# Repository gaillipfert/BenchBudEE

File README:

The BenchBudEE is the project for the Session 1 course on ContextualElectronics.com. It is a flexible bench multitool, intended to teach a wide range of analog and digital technique and easily interface to the Arduino platform. The hardware files are licensed as Open Source Hardware, so anyone will be able to take the files and modify them (with attribution) or manufacture a finished board. All design files are available on GitHub. The board has the following subcircuits:

    A high level analog input measurement circuit (for +/- 10V and thermocouple measurement)
    A programmable current output.
    A PWM fan control output.
    Power conditioning and fixed voltage output circuits.
    A relay control circuit.
    An LED string driver.

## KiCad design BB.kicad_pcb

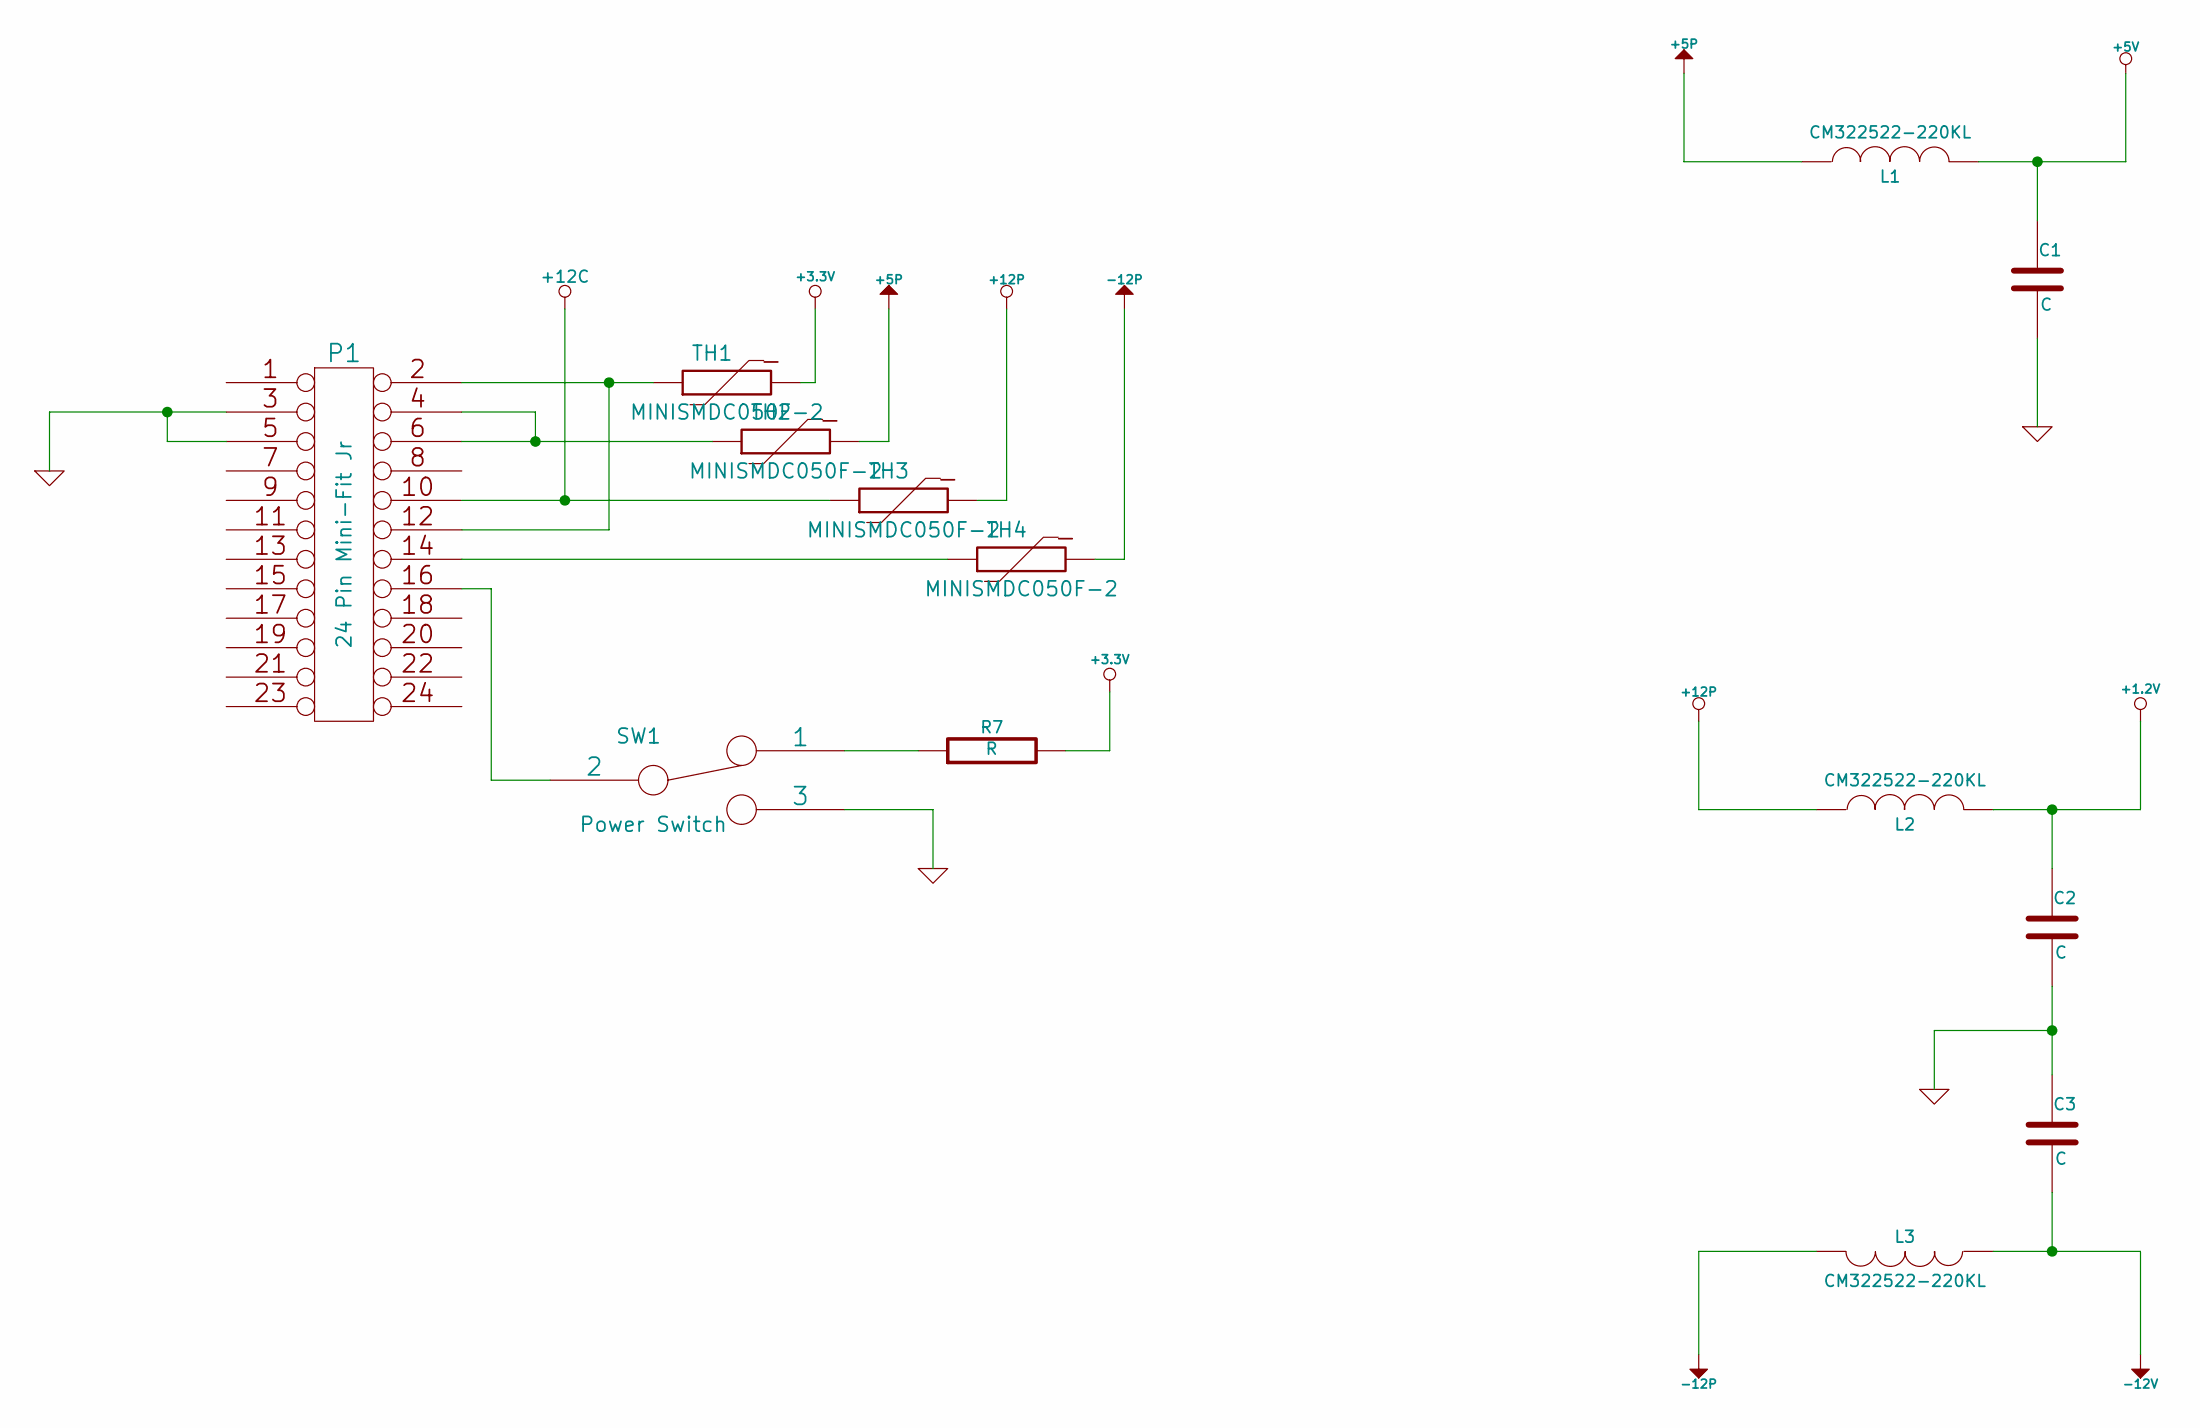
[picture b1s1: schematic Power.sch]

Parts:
C1, C2, C3: C
L1, L2, L3: CM322522-220KL; MFG Part Number CM322522-220KL
P1: 24 Pin Mini-Fit Jr; MFG Part Number 39-30-1240
R7: R
SW1: Power Switch; MFG Part Number OS102011MA1QN1
TH1, TH2, TH3, TH4: MINISMDC050F-2; MFG Part Number MINISMDC050F-2

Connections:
+1.2V: C2.1, L2.2; also elsewhere on the board
+3.3V: R7.2, TH1.2; also elsewhere on the board
+5P: L1.1, TH2.2; also elsewhere on the board
+5V: C1.1, L1.2; also elsewhere on the board
+12C: P1.10, TH3.1; also elsewhere on the board
+12P: L2.1, TH3.2; also elsewhere on the board
-12P: L3.2, TH4.2
-12V: C3.2, L3.1; also elsewhere on the board
GND: C1.2, C2.2, C3.1, P1.3, P1.5, SW1.3; also elsewhere on the board
unnamed: P1.4, P1.6, TH2.1
unnamed: P1.2, P1.12, TH1.1
unnamed: P1.14, TH4.1
unnamed: P1.16, SW1.2
unnamed: R7.1, SW1.1

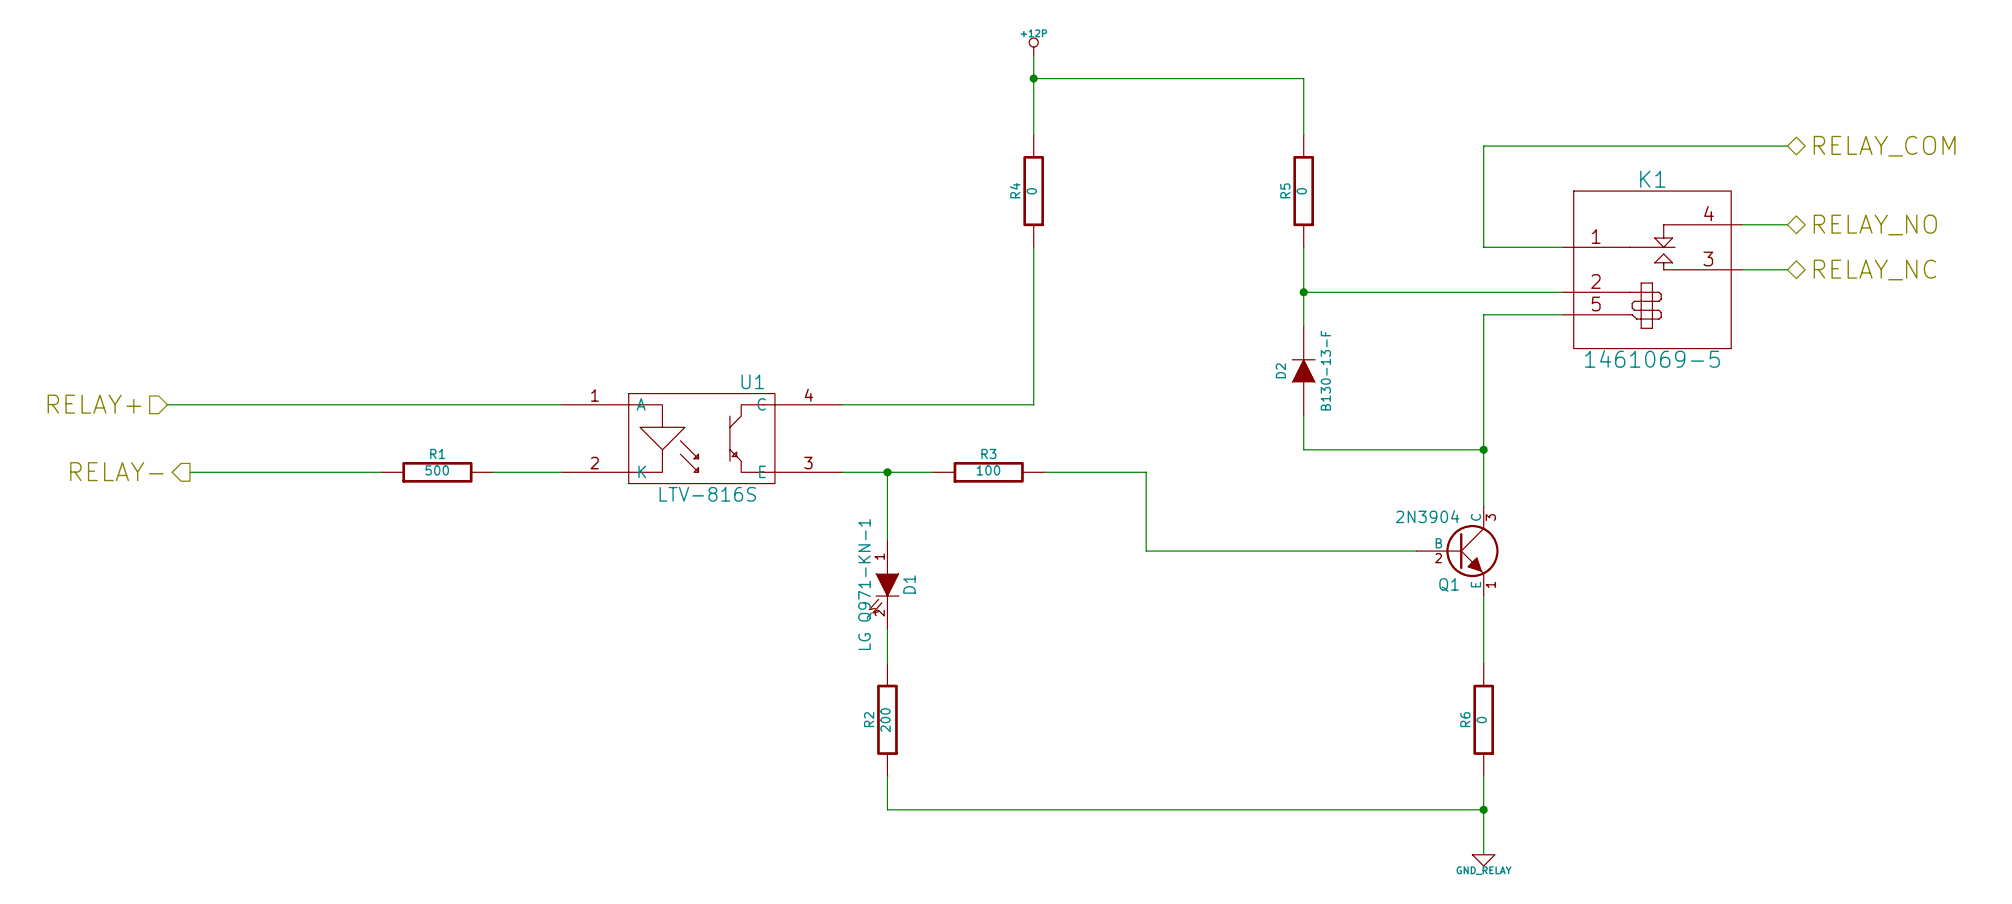
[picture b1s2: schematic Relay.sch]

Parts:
D1: LG Q971-KN-1; MFG Part Number LG Q971-KN-1
D2: B130-13-F; MFG Part Number B130-13-F
K1: 1461069-5; MFG Part Number 1461069-5
Q1: 2N3904; MFG Part Number MMBT3904-7-F
R1: 500
R2: 200
R3: 100
R4, R5, R6: 0
U1: LTV-816S; MFG Part Number LTV-816S

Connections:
+12P: R4.2, R5.2; also elsewhere on the board
/Arduino/RELAY+: U1.1 (A); also elsewhere on the board
/Arduino/RELAY-: R1.1; also elsewhere on the board
/Relay/RELAY_COM: K1.1 (com); also elsewhere on the board
/Relay/RELAY_NC: K1.3 (no); also elsewhere on the board
/Relay/RELAY_NO: K1.4 (NC); also elsewhere on the board
GND_RELAY: R2.1, R6.1
unnamed: D1.1 (A), R3.1, U1.3 (E)
unnamed: D1.2 (K), R2.2
unnamed: D2.1 (A), K1.5 (coil1), Q1.3 (C)
unnamed: D2.2 (K), K1.2 (coil+), R5.1
unnamed: Q1.1 (E), R6.2
unnamed: Q1.2 (B), R3.2
unnamed: R1.2, U1.2 (K)
unnamed: R4.1, U1.4 (C)

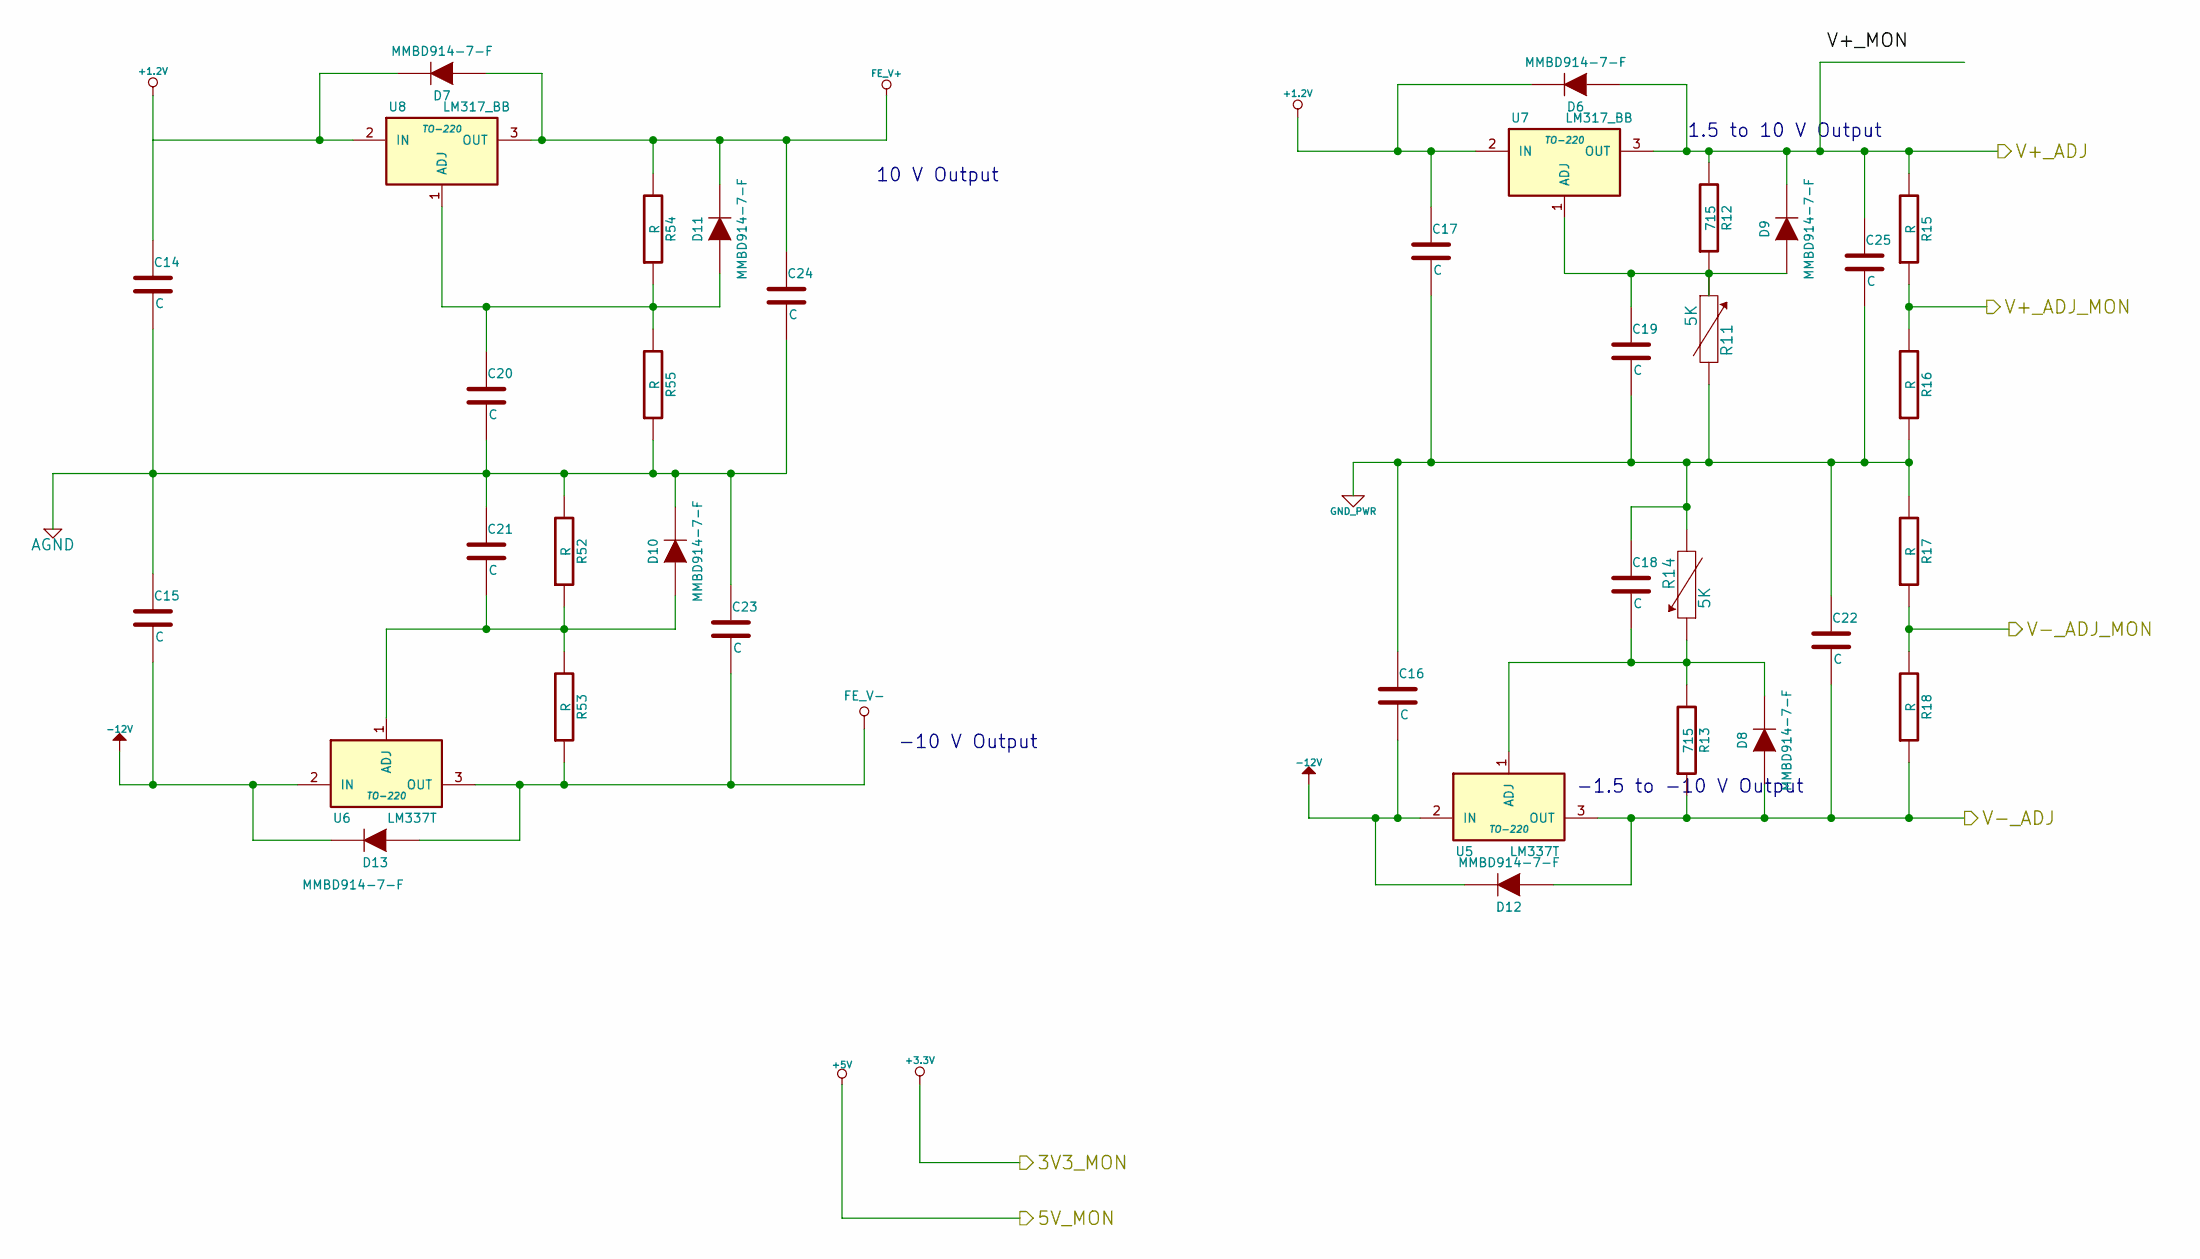
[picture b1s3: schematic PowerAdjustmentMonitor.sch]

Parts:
C14, C15, C16, C17, C18, C19, C20, C21, C22, C23, C24, C25: C
D6, D7, D8, D9, D10, D11, D12, D13: MMBD914-7-F; MFG Part Number MMBD914-7-F
R11, R14: 5K
R12, R13: 715
R15, R16, R17, R18, R52, R53, R54, R55: R
U5, U6: LM337T; TO-220
U7, U8: LM317_BB; TO-220

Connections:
+1.2V: C14.1, C17.1, D6.2 (K), U7.2 (IN); also elsewhere on the board
-12V: C15.2, C16.2, D12.2 (K), D13.2 (K), U5.2 (IN), U6.2 (IN); also elsewhere on the board
/Arduino/V+_ADJ_MON: R15.1, R16.2; also elsewhere on the board
/Arduino/V-_ADJ_MON: R17.1, R18.2; also elsewhere on the board
/PowerAdjustmentMonitor/V+_ADJ: C25.1, D6.1 (A), D9.2 (K), R12.2, R15.2, U7.3 (OUT); also elsewhere on the board
/PowerAdjustmentMonitor/V-_ADJ: C22.2, D8.1 (A), D12.1 (A), R13.1, R18.1, U5.3 (OUT); also elsewhere on the board
AGND: C14.2, C15.1, C20.2, C21.1, C23.1, C24.2, D10.2 (K), R52.2, R55.1; also elsewhere on the board
FE_V+: C24.1, D7.1 (A), D11.2 (K), R54.2, U8.3 (OUT); also elsewhere on the board
FE_V-: C23.2, D13.1 (A), R53.1, U6.3 (OUT); also elsewhere on the board
GND_PWR: C16.1, C17.2, C18.1, C19.2, C22.1, C25.2, R11.2, R14.2, R16.1, R17.2; also elsewhere on the board
unnamed: C18.2, D8.2 (K), R13.2, R14.1, U5.1 (ADJ)
unnamed: C19.1, D9.1 (A), R11.1, R12.1, U7.1 (ADJ)
unnamed: C20.1, D11.1 (A), R54.1, R55.2, U8.1 (ADJ)
unnamed: C21.2, D10.1 (A), R52.1, R53.2, U6.1 (ADJ)
unnamed: D7.2 (K), U8.2 (IN)

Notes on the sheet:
1.5 to 10 V Output
10 V Output
-10 V Output
-1.5 to -10 V Output

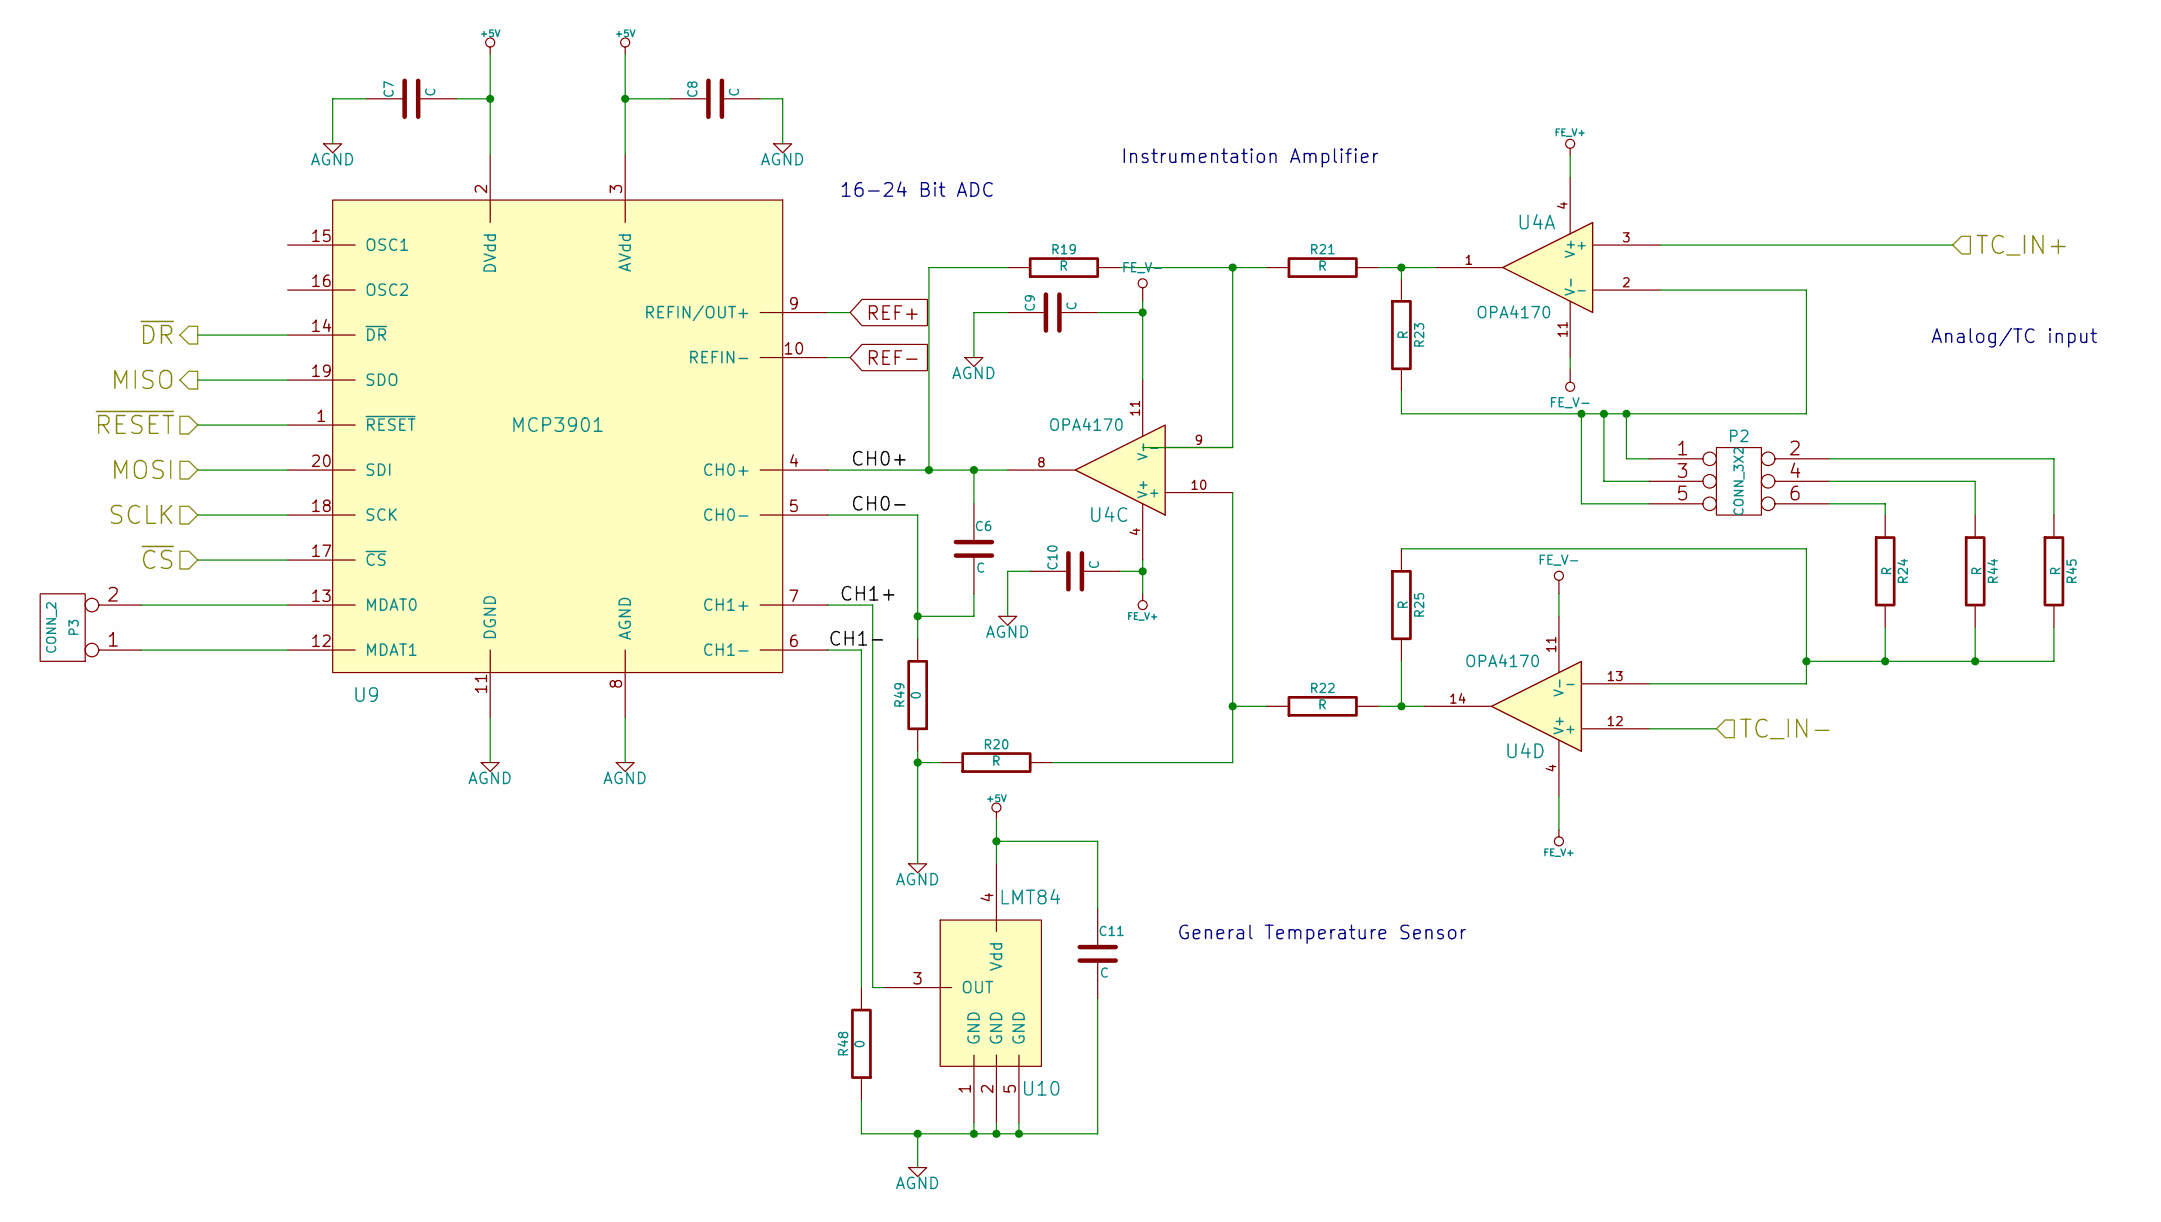
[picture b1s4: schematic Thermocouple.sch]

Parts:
C6, C7, C8, C9, C10, C11: C
P2: CONN_3X2
P3: CONN_2
R19, R20, R21, R22, R23, R24, R25, R44, R45: R
R48, R49: 0
U4: OPA4170
U9: MCP3901
U10: LMT84

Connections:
+5V: C7.2, C8.1, C11.1, U9.2 (DVdd), U9.3 (AVdd), U10.4 (Vdd); also elsewhere on the board
/Arduino/MISO: U9.19 (SDO); also elsewhere on the board
/Arduino/MOSI: U9.20 (SDI); also elsewhere on the board
/Arduino/SCLK: U9.18 (SCK); also elsewhere on the board
/Arduino/~ADC_CS: U9.17 (~CS); also elsewhere on the board
/Arduino/~DR: U9.14 (~DR); also elsewhere on the board
/Arduino/~RESET: U9.1 (~RESET); also elsewhere on the board
/TerminalBlock/TC_IN+: U4.3 (+); also elsewhere on the board
/TerminalBlock/TC_IN-: U4.12 (+); also elsewhere on the board
/Thermocouple/CH0+: C6.1, R19.1, U4.8, U9.4 (CH0+)
/Thermocouple/CH0-: C6.2, R49.2, U9.5 (CH0-)
/Thermocouple/CH1+: U9.7 (CH1+), U10.3 (OUT)
/Thermocouple/CH1-: R48.2, U9.6 (CH1-)
AGND: C7.1, C8.2, C9.1, C10.1, C11.2, R20.1, R48.1, R49.1, U9.8 (AGND), U9.11 (DGND), U10.1 (GND), U10.2 (GND), U10.5 (GND); also elsewhere on the board
FE_V+: C10.2, U4.4 (V+); also elsewhere on the board
FE_V-: C9.2, U4.11 (V-); also elsewhere on the board
unnamed: P2.1, P2.3, P2.5, R23.2, U4.2 (-)
unnamed: P2.2, R45.1
unnamed: P2.4, R44.1
unnamed: P2.6, R24.1
unnamed: P3.1, U9.12 (MDAT1)
unnamed: P3.2 (PM), U9.13 (MDAT0)
unnamed: R19.2, R21.1, U4.9 (-)
unnamed: R20.2, R22.1, U4.10 (+)
unnamed: R21.2, R23.1, U4.1
unnamed: R22.2, R25.2, U4.14
unnamed: R24.2, R25.1, R44.2, R45.2, U4.13 (-)
REF+: U9.9 (REFIN/OUT+)
REF-: U9.10 (REFIN-)

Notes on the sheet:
General Temperature Sensor
Instrumentation Amplifier
16-24 Bit ADC
Analog/TC input

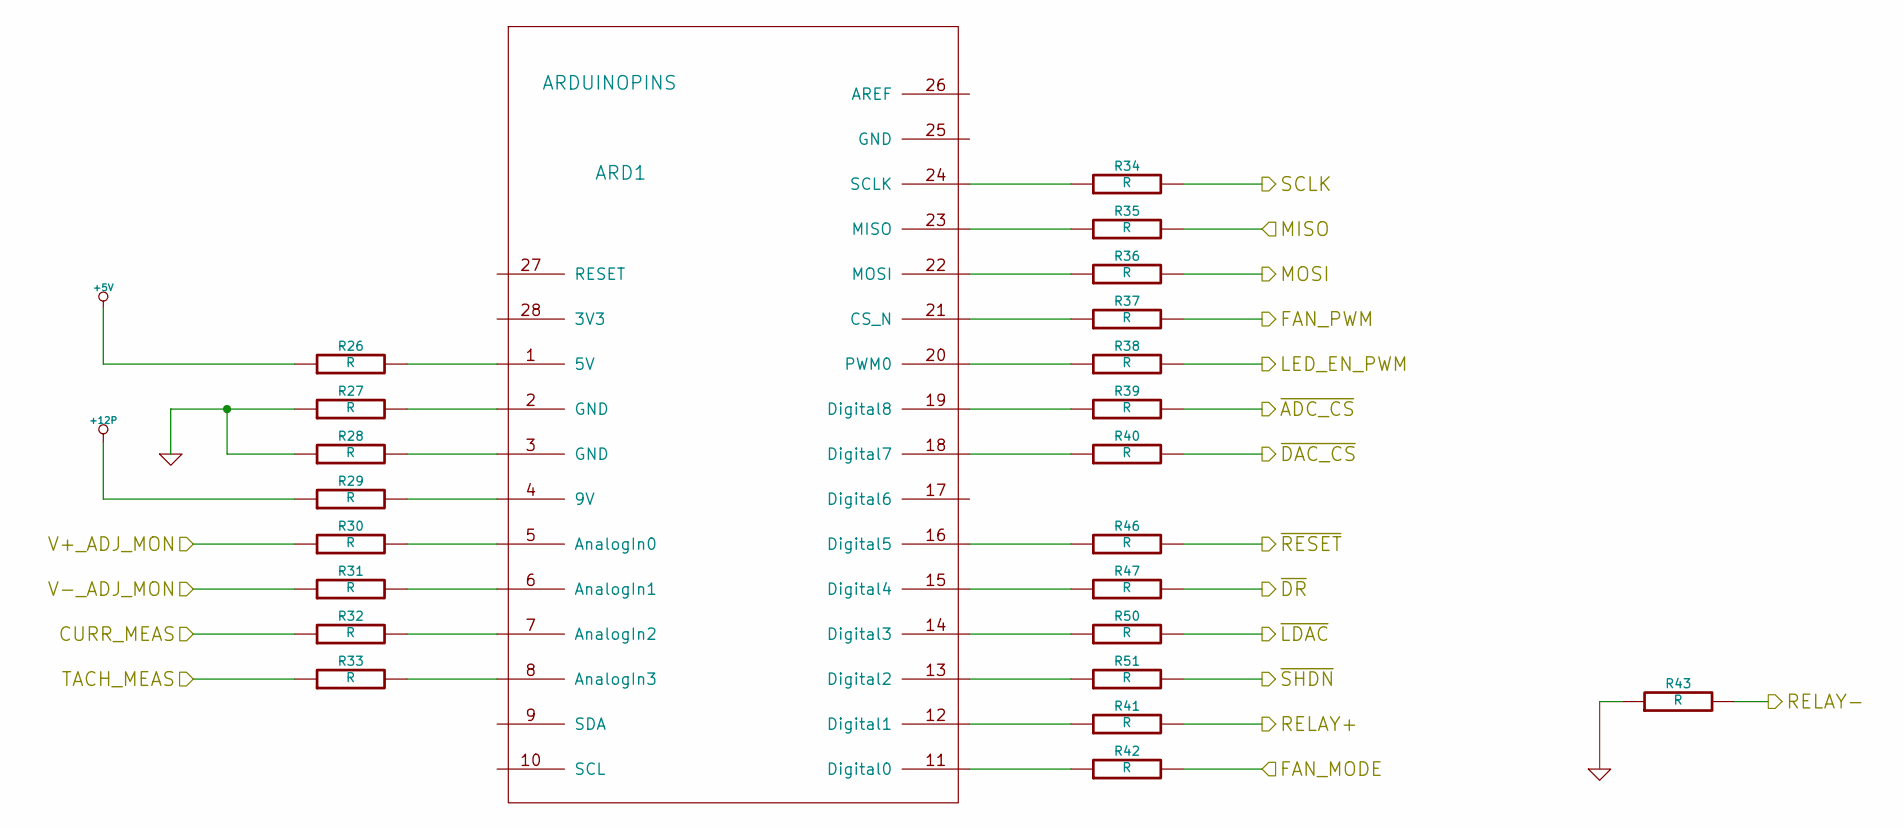
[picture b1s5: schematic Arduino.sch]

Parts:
ARD1: ARDUINOPINS
R26, R27, R28, R29, R30, R31, R32, R33, R34, R35, R36, R37, R38, R39, R40, R41, R42, R43, R46, R47, R50, R51: R

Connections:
+5V: R26.1; also elsewhere on the board
+12P: R29.1; also elsewhere on the board
/Arduino/CURR_MEAS: R32.1; also elsewhere on the board
/Arduino/FAN_MODE: R42.2; also elsewhere on the board
/Arduino/FAN_PWM: R37.2; also elsewhere on the board
/Arduino/LED_EN_PWM: R38.2; also elsewhere on the board
/Arduino/MISO: R35.2; also elsewhere on the board
/Arduino/MOSI: R36.2; also elsewhere on the board
/Arduino/RELAY+: R41.2; also elsewhere on the board
/Arduino/RELAY-: R43.2; also elsewhere on the board
/Arduino/SCLK: R34.2; also elsewhere on the board
/Arduino/V+_ADJ_MON: R30.1; also elsewhere on the board
/Arduino/V-_ADJ_MON: R31.1; also elsewhere on the board
/Arduino/~ADC_CS: R39.2; also elsewhere on the board
/Arduino/~DR: R47.2; also elsewhere on the board
/Arduino/~LDAC: R50.2; also elsewhere on the board
/Arduino/~RESET: R46.2; also elsewhere on the board
/Arduino/~SHDN: R51.2; also elsewhere on the board
/Fan/CS_N: R40.2; also elsewhere on the board
/Fan/TACH_IN: R33.1; also elsewhere on the board
GND: R27.1, R28.1, R43.1; also elsewhere on the board
unnamed: ARD1.1 (5V), R26.2
unnamed: ARD1.2 (GND), R27.2
unnamed: ARD1.3 (GND), R28.2
unnamed: ARD1.4 (9V), R29.2
unnamed: ARD1.5 (AnalogIn0), R30.2
unnamed: ARD1.6 (AnalogIn1), R31.2
unnamed: ARD1.7 (AnalogIn2), R32.2
unnamed: ARD1.8 (AnalogIn3), R33.2
unnamed: ARD1.11 (Digital0), R42.1
unnamed: ARD1.12 (Digital1), R41.1
unnamed: ARD1.13 (Digital2), R51.1
unnamed: ARD1.14 (Digital3), R50.1
unnamed: ARD1.15 (Digital4), R47.1
unnamed: ARD1.16 (Digital5), R46.1
unnamed: ARD1.18 (Digital7), R40.1
unnamed: ARD1.19 (Digital8), R39.1
unnamed: ARD1.20 (PWM0), R38.1
unnamed: ARD1.21 (CS_N), R37.1
unnamed: ARD1.22 (MOSI), R36.1
unnamed: ARD1.23 (MISO), R35.1
unnamed: ARD1.24 (SCLK), R34.1

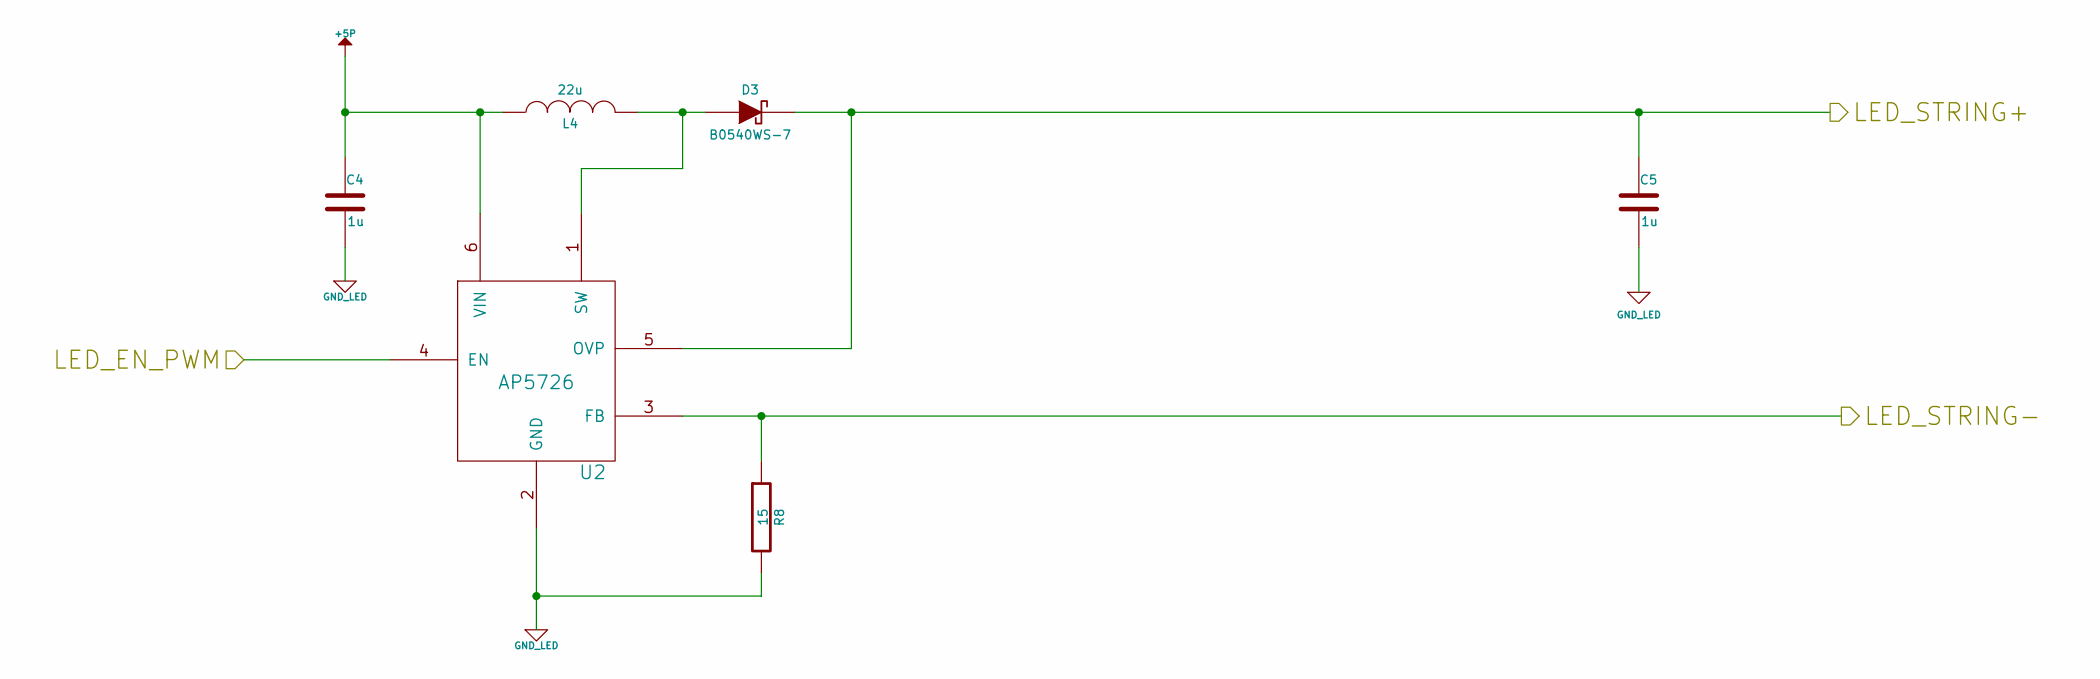
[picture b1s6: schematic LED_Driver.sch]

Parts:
C4, C5: 1u
D3: B0540WS-7; MFG Part Number B0540WS-7
L4: 22u; MFG Part Number NR4012T220M
R8: 15
U2: AP5726

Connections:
+5P: C4.1, L4.1, U2.6 (VIN); also elsewhere on the board
/Arduino/LED_EN_PWM: U2.4 (EN); also elsewhere on the board
/LED_Driver/LED_STRING+: C5.1, D3.2 (K), U2.5 (OVP); also elsewhere on the board
/LED_Driver/LED_STRING-: R8.1, U2.3 (FB); also elsewhere on the board
GND_LED: C4.2, C5.2, R8.2, U2.2 (GND)
unnamed: D3.1 (A), L4.2, U2.1 (SW)

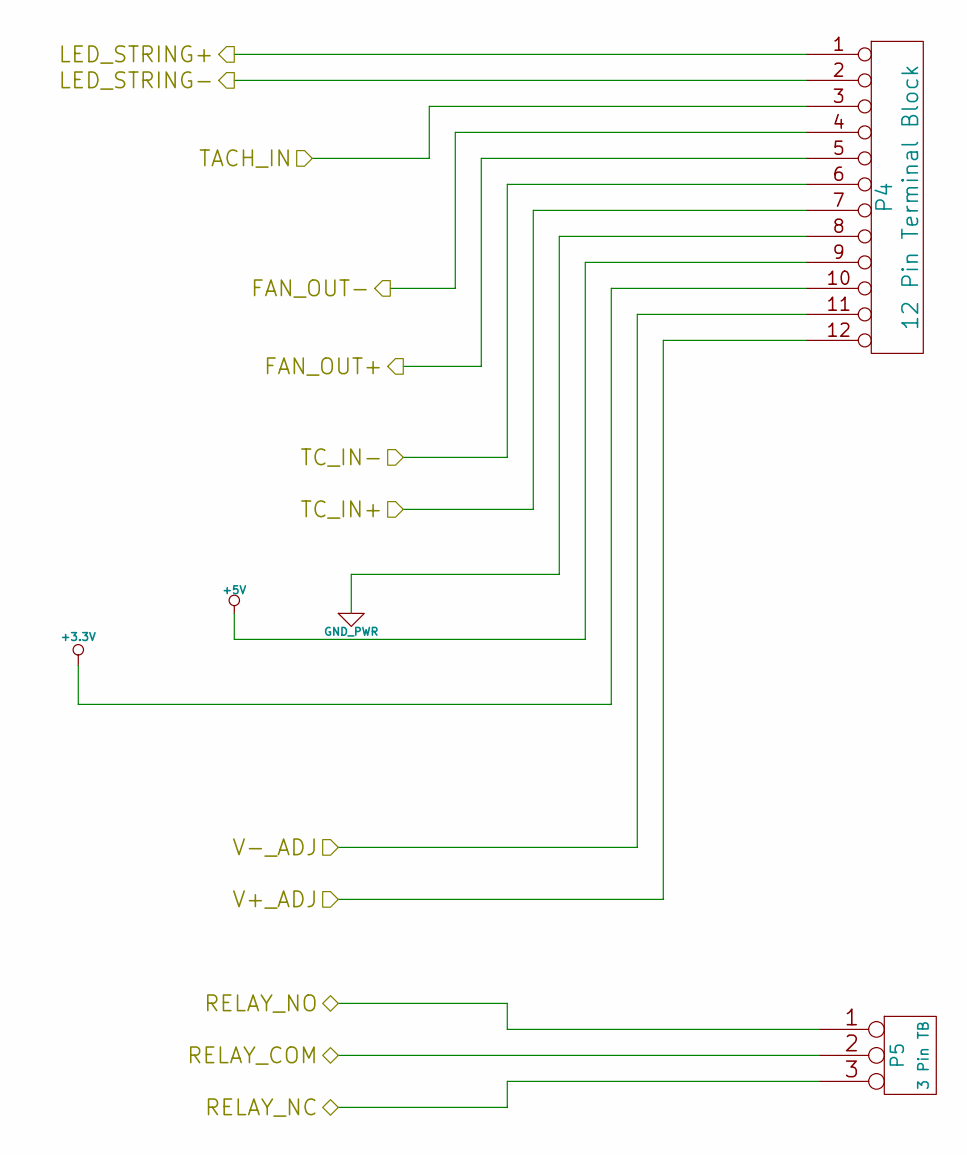
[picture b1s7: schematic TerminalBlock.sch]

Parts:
P4: 12 Pin Terminal Block; MFG Part Number OSTTE120104
P5: 3 Pin TB; MFG Part Number 1935174

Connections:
+3.3V: P4.10; also elsewhere on the board
+5V: P4.9; also elsewhere on the board
/Fan/FAN_OUT+: P4.5; also elsewhere on the board
/Fan/FAN_OUT-: P4.4; also elsewhere on the board
/Fan/TACH_IN: P4.3; also elsewhere on the board
/LED_Driver/LED_STRING+: P4.1; also elsewhere on the board
/LED_Driver/LED_STRING-: P4.2; also elsewhere on the board
/PowerAdjustmentMonitor/V+_ADJ: P4.12; also elsewhere on the board
/PowerAdjustmentMonitor/V-_ADJ: P4.11; also elsewhere on the board
/Relay/RELAY_COM: P5.2 (PM); also elsewhere on the board
/Relay/RELAY_NC: P5.3; also elsewhere on the board
/Relay/RELAY_NO: P5.1; also elsewhere on the board
/TerminalBlock/TC_IN+: P4.7; also elsewhere on the board
/TerminalBlock/TC_IN-: P4.6; also elsewhere on the board
GND_PWR: P4.8; also elsewhere on the board

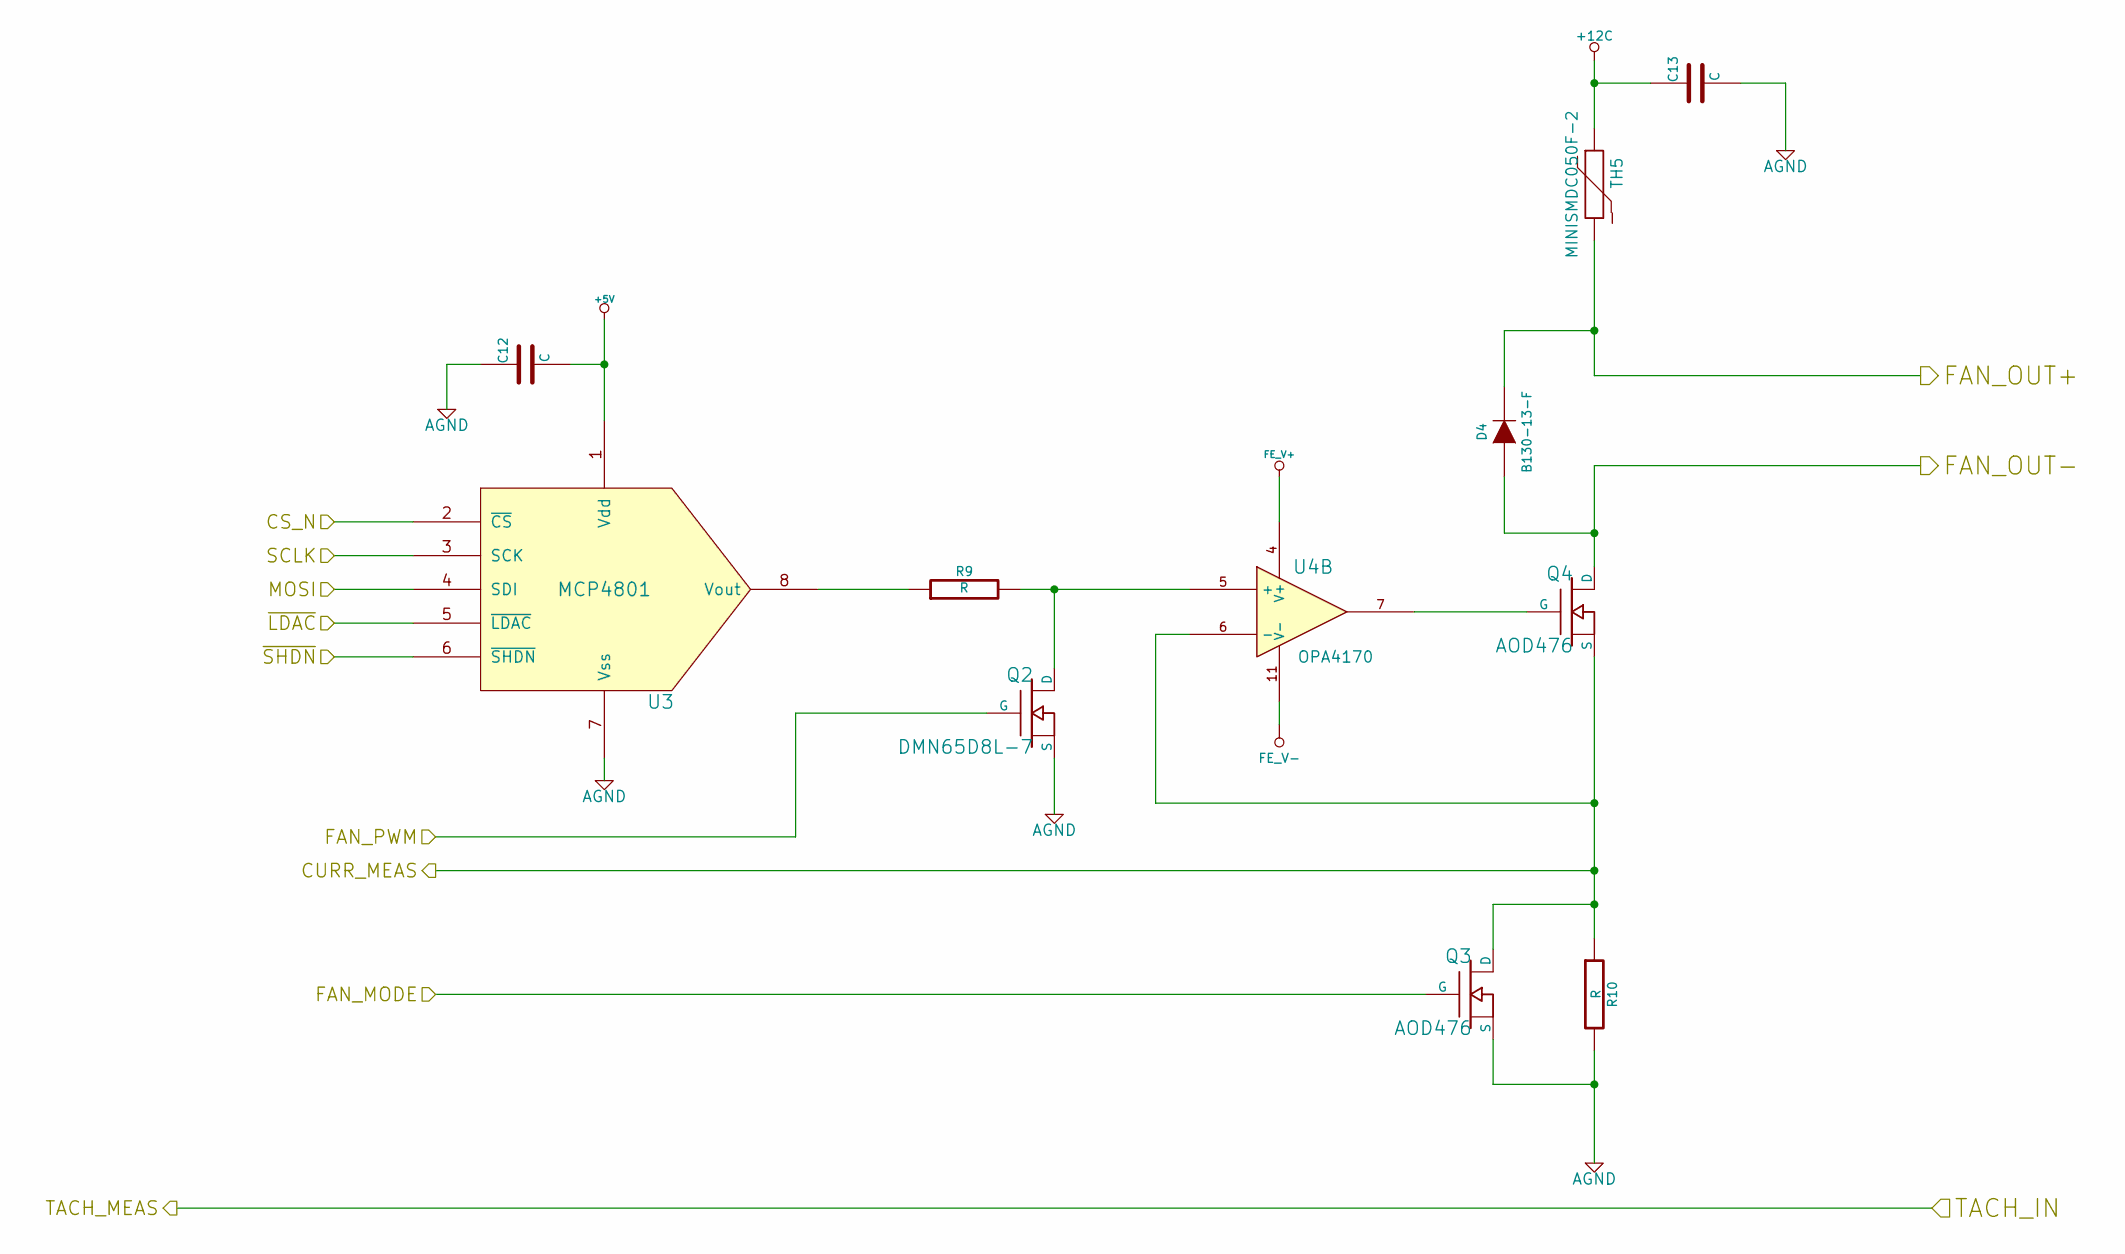
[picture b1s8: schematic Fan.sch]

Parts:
C12, C13: C
D4: B130-13-F; MFG Part Number B130-13-F
Q2: DMN65D8L-7; MFG Part Number DMN65D8L-7
Q3, Q4: AOD476; MFG Part Number AOD476
R9, R10: R
TH5: MINISMDC050F-2; MFG Part Number MINISMDC050F-2
U3: MCP4801
U4: OPA4170

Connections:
+5V: C12.2, U3.1 (Vdd); also elsewhere on the board
+12C: C13.1, TH5.1; also elsewhere on the board
/Arduino/CURR_MEAS: Q3.2 (D), Q4.3 (S), R10.1, U4.6 (-); also elsewhere on the board
/Arduino/FAN_MODE: Q3.1 (G); also elsewhere on the board
/Arduino/FAN_PWM: Q2.G; also elsewhere on the board
/Arduino/MOSI: U3.4 (SDI); also elsewhere on the board
/Arduino/SCLK: U3.3 (SCK); also elsewhere on the board
/Arduino/~LDAC: U3.5 (~LDAC); also elsewhere on the board
/Arduino/~SHDN: U3.6 (~SHDN); also elsewhere on the board
/Fan/CS_N: U3.2 (~CS); also elsewhere on the board
/Fan/FAN_OUT+: D4.2 (K), TH5.2; also elsewhere on the board
/Fan/FAN_OUT-: D4.1 (A), Q4.2 (D); also elsewhere on the board
AGND: C12.1, C13.2, Q2.3 (S), Q2.S, Q3.3 (S), R10.2, U3.7 (Vss); also elsewhere on the board
FE_V+: U4.4 (V+); also elsewhere on the board
FE_V-: U4.11 (V-); also elsewhere on the board
unnamed: Q2.2 (D), Q2.D, R9.2, U4.5 (+)
unnamed: Q4.1 (G), U4.7
unnamed: R9.1, U3.8 (Vout)
